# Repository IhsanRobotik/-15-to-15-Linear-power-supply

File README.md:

# +/-15 V Linear Power Supply

A compact linear bench supply with a custom PCB and enclosure. The front panel provides a fixed **+5 V** output and adjustable outputs labeled **0 to 15 V** and **-15 to 0 V**.

## PCB and schematic

| PCB, component side | PCB, solder side |
|:--:|:--:|
|  |  |

## Enclosure views

| Front panel | Rear panel |
|:--:|:--:|
|  |  |

## Project files

- [KiCad project](Power%20supply.kicad_pro)
- [Schematic](Power%20supply.kicad_sch)
- [PCB layout](Power%20supply.kicad_pcb)
- [Enclosure STEP model](exports/3d/Power%20supply.step)
- [PDF drawing](exports/pdf/PSU.pdf)

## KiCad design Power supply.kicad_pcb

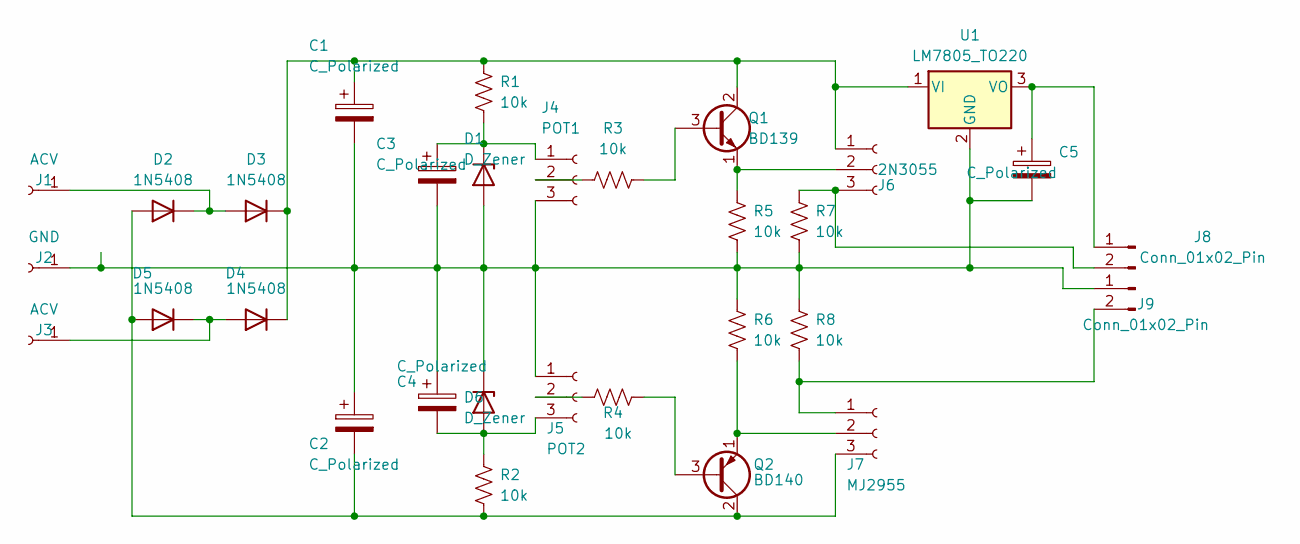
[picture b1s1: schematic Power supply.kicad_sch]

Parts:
C1, C2, C3, C4: C_Polarized; CP_Radial_D18.0mm_P7.50mm
C5: C_Polarized; CP_Radial_D6.3mm_P2.50mm
D1, D6: D_Zener; D_DO-41_SOD81_P10.16mm_Horizontal
D2, D3, D4, D5: 1N5408; D_DO-201AD_P15.24mm_Horizontal
J1, J3: ACV; MountingHole_2.5mm_Pad
J2: GND; MountingHole_2.5mm_Pad
J4: POT1; SolderWire-1sqmm_1x03_P5.4mm_D1.4mm_OD2.7mm
J5: POT2; SolderWire-1sqmm_1x03_P5.4mm_D1.4mm_OD2.7mm
J6: 2N3055; SolderWire-1sqmm_1x03_P5.4mm_D1.4mm_OD2.7mm
J7: MJ2955; SolderWire-1sqmm_1x03_P5.4mm_D1.4mm_OD2.7mm
J8, J9: Conn_01x02_Pin; SolderWire-1sqmm_1x02_P5.4mm_D1.4mm_OD2.7mm
Q1: BD139; TO-126-3_Vertical
Q2: BD140; TO-126-3_Vertical
R1, R2, R3, R4, R5, R6, R7, R8: 10k; R_Axial_DIN0414_L11.9mm_D4.5mm_P5.08mm_Vertical
U1: LM7805_TO220; TO-220-3_Vertical

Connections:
unnamed: C1.2, C2.1, C3.2, C4.1, C5.2, D1.2 (A), D6.1 (K), J2.1, J4.3, J5.1, J9.1, R5.1, R6.2, R7.1, R8.2, U1.2 (GND)
unnamed: C3.1, D1.1 (K), J4.1, R1.2
unnamed: C2.2, D2.2 (A), D5.2 (A), J7.3, Q2.2 (C), R2.2
unnamed: D2.1 (K), D3.2 (A), J1.1
unnamed: C1.1, D3.1 (K), D4.1 (K), J6.1, Q1.2 (C), R1.1, U1.1 (VI)
unnamed: D4.2 (A), D5.1 (K), J3.1
unnamed: C4.2, D6.2 (A), J5.3, R2.1
unnamed: J4.2, R3.1
unnamed: J5.2, R4.1
unnamed: J6.2, Q1.1 (E), R5.2
unnamed: J6.3, J8.2, R7.2
unnamed: J7.1, J9.2, R8.1
unnamed: J7.2, Q2.1 (E), R6.1
unnamed: C5.1, J8.1, U1.3 (VO)
unnamed: Q1.3 (B), R3.2
unnamed: Q2.3 (B), R4.2

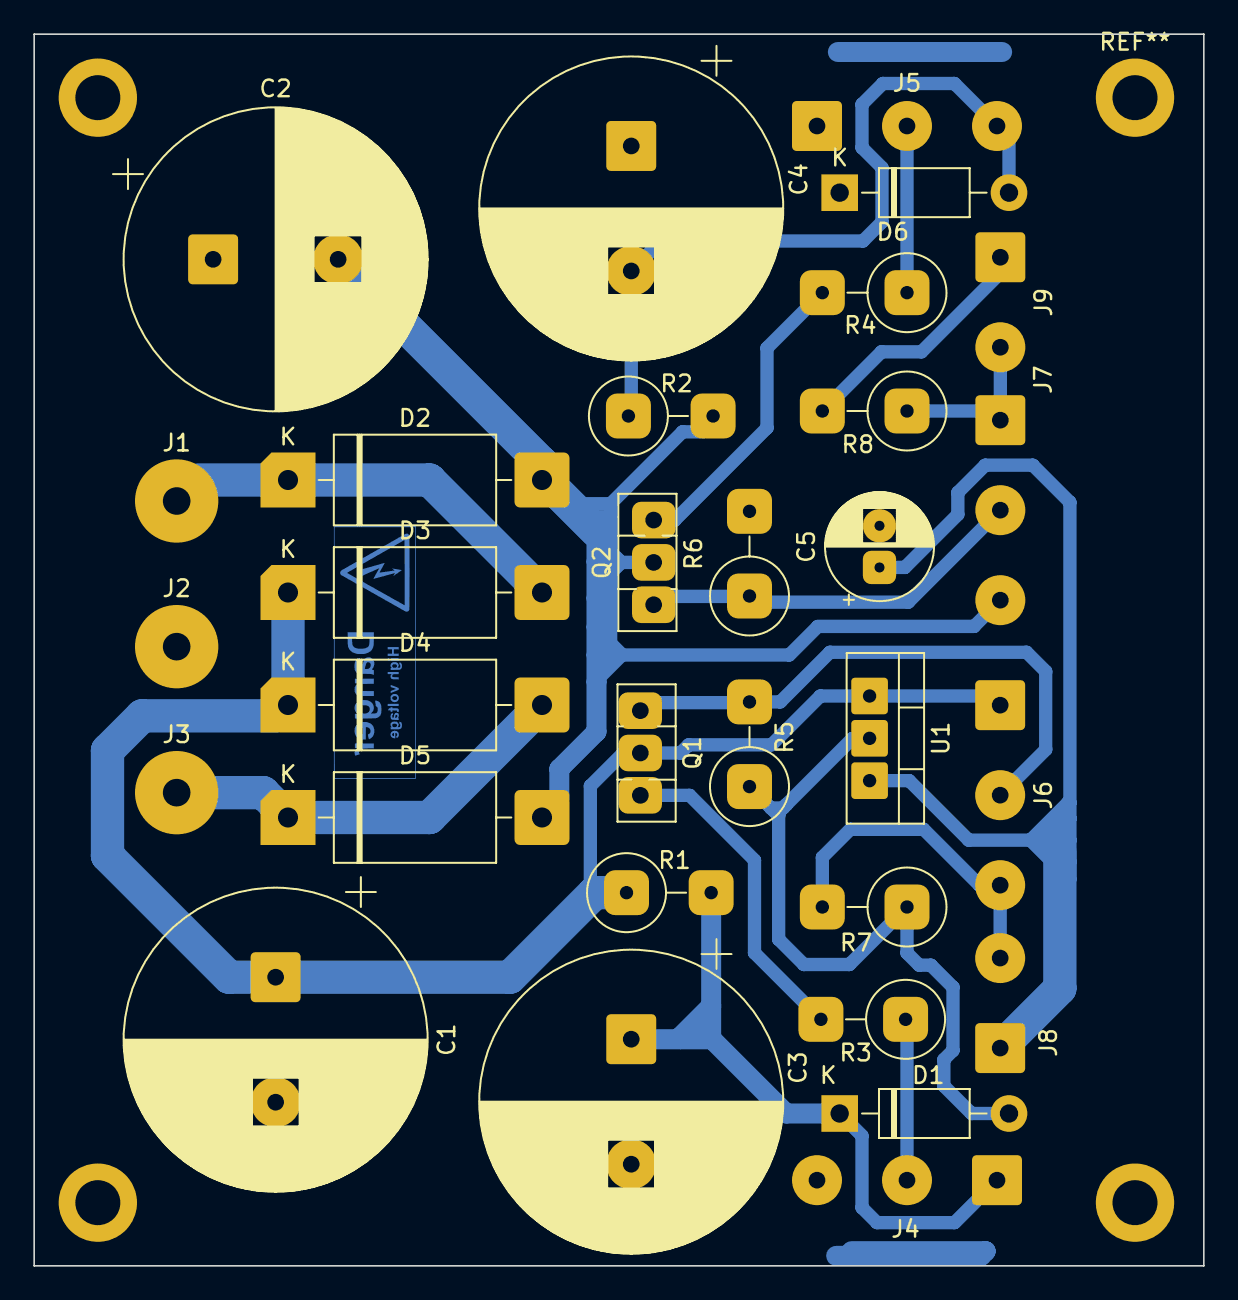
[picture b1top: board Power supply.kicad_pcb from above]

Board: 2 copper layers, 70.2 x 73.9 mm, 31 parts (0 on the bottom side), 16 nets.
